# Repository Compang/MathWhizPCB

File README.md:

# MathWhizPCB
PCB designed for ONU research

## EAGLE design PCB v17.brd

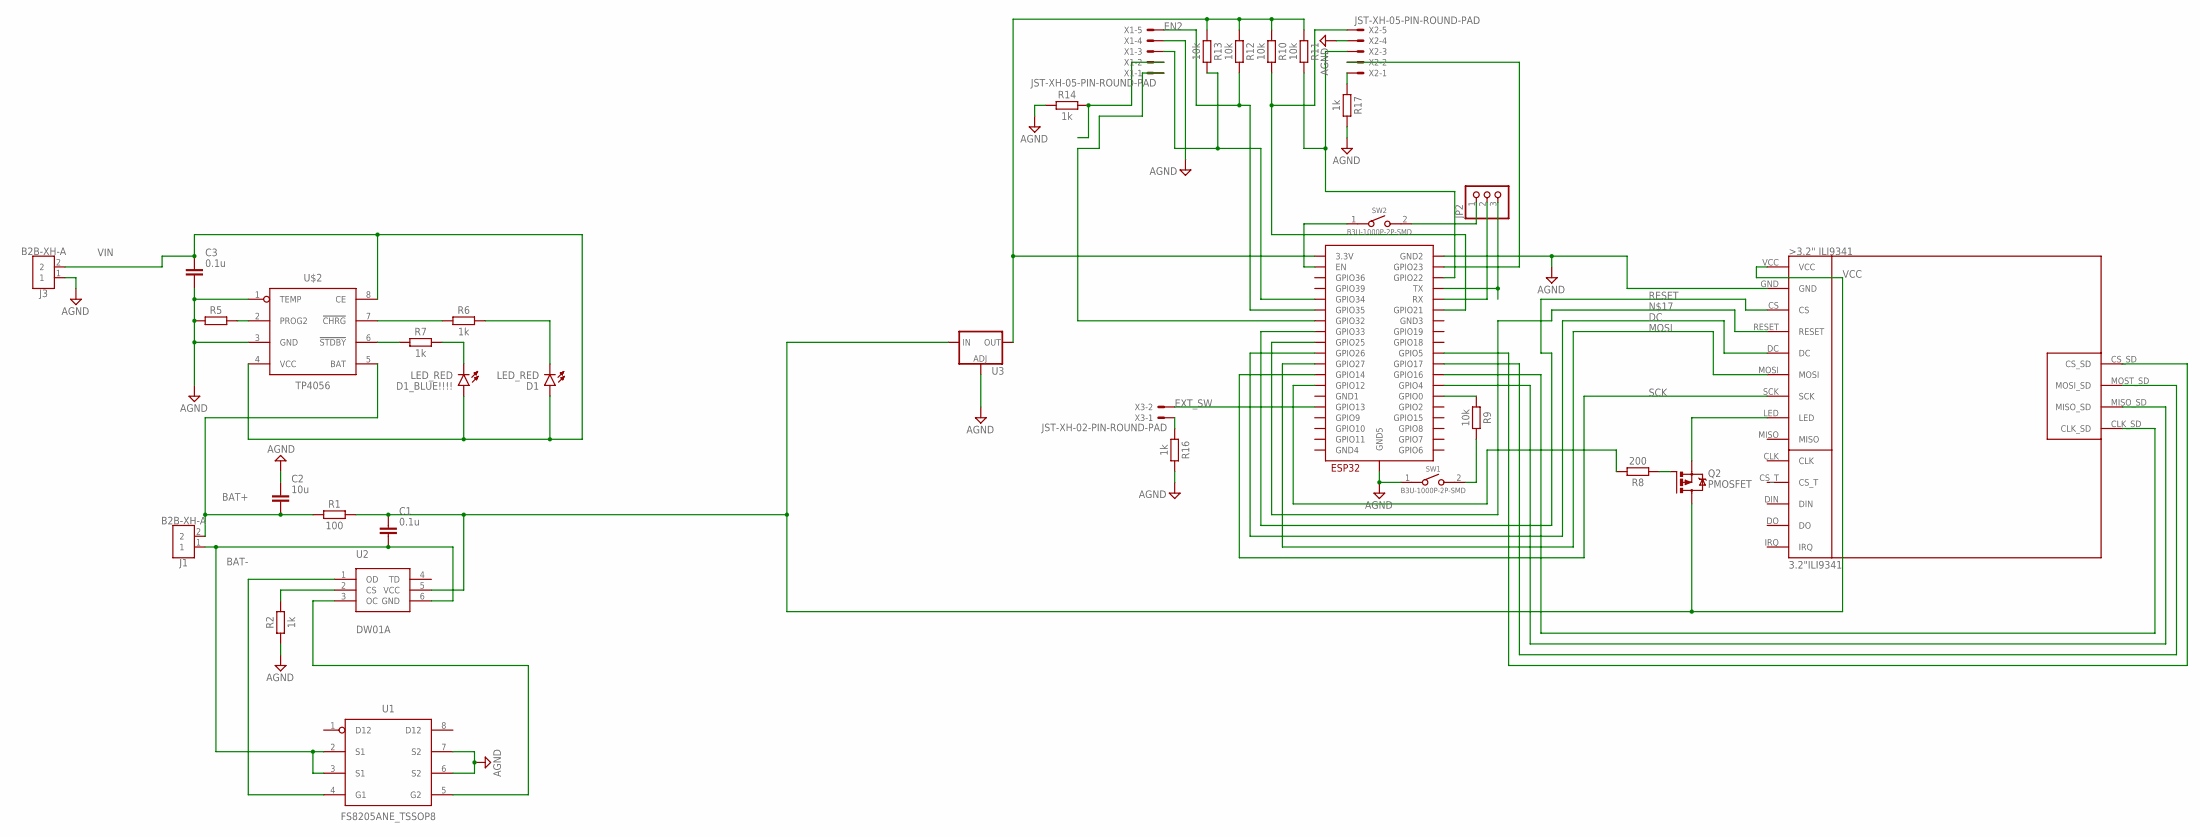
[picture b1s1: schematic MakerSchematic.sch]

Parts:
C1, C3: 0.1u; CAPC1608X85
C2: 10u; CAPC1608X85
D1, D1_BLUE!!!!: LED_RED; LEDC2012X110N_FLAT-R
J1, J3: B2B-XH-A
JP2: PINHD-1X3/90; 1X03/90
Q2: PMOSFET; SOT23
R1: 100; RESC2012X65
R2, R6, R7, R14, R16, R17: 1k; RESC1608X60
R5: R_CHIP-0603(1608-METRIC); RESC1608X60
R8: 200; RESC2012X65
R9, R10, R11, R12, R13: 10k; RESC1608X60
SW1, SW2: B3U-1000P-2P-SMD; SW2-2.6-3.0X2.5X1.2+0.4MM
U1: FS8205ANE_TSSOP8; SOP65P640X120-8
U2: DW01A
U3: V_REG_LM1117SOT223; SOT223
U$1: ESP32-WROOM
U$2: TP4056; SOIC127P601X152-8N
U$3: 3.2"ILI9341
X1, X2: JST-XH-05-PIN-ROUND-PAD; JST-XH-05-PACKAGE-ROUND-PAD
X3: JST-XH-02-PIN-ROUND-PAD; JST-XH-02-PACKAGE-ROUND-PAD

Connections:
AGND: C2.1, C3.2, J3.1, R2.1, R5.1, R14.1, R16.2, R17.2, SW1.1, U1.6 (S2), U1.7 (S2), U3.1 (ADJ), U$1.GND2, U$1.GND5, U$2.1 (TEMP), U$2.3 (GND), U$3.GND, X1.4, X2.4
BAT+: C2.2, J1.2, R1.1, U$2.5 (BAT)
BAT-: C1.2, J1.1, U1.2 (S1), U1.3 (S1), U2.6 (GND)
D12: U1.8 (D12)
DC: U$1.IO26 (GPIO26), U$3.DC
EN2: R12.2, U$1.IO35 (GPIO35), X1.5
EXT_SW: U$1.IO13 (GPIO13), X3.2
MOSI: U$1.IO27 (GPIO27), U$3.MOSI
unnamed: R10.1, R11.1, R12.1, R13.1, U3.2 (OUT), U3.4 (OUT), U$1.3V3 (3.3V)
unnamed: U1.4 (G1), U2.1 (OD)
unnamed: U1.5 (G2), U2.3 (OC)
unnamed: R2.2, U2.2 (CS)
unnamed: R6.1, U$2.7 (!CHRG)
unnamed: R5.2, U$2.2 (PROG2)
unnamed: D1_BLUE!!!!.C, R7.2
unnamed: R7.1, U$2.6 (!STDBY)
unnamed: D1.C, R6.2
unnamed: R9.1, U$1.IO0 (GPIO0)
unnamed: JP2.2, U$1.RX
unnamed: JP2.3, U$1.TX
unnamed: SW2.1, U$1.EN
unnamed: R8.2, U$1.IO12 (GPIO12)
unnamed: U$1.IO25 (GPIO25), U$3.RESET
unnamed: R17.1, X2.1
unnamed: Q2.1 (G), R8.1
unnamed: JP2.1, SW2.2
unnamed: R10.2, U$1.IO21 (GPIO21), X2.5
unnamed: R13.2, U$1.IO34 (GPIO34), X1.3
unnamed: U$1.IO23 (GPIO23), X2.2
unnamed: U$1.IO32 (GPIO32), X1.1
unnamed: R9.2, SW1.2
unnamed: Q2.2 (S), U$3.LED
unnamed: U$1.IO17 (GPIO17), U$3.MOST_SD (MOSI_SD)
unnamed: U$1.IO16 (GPIO16), U$3.CLK_SD
unnamed: R14.2, X1.2
unnamed: R16.1, X3.1
unnamed: U$1.IO4 (GPIO4), U$3.MISO_SD
unnamed: U$1.IO5 (GPIO5), U$3.CS_SD
RESET: U$1.IO33 (GPIO33), U$3.CS
SCK: U$1.IO14 (GPIO14), U$3.SCK
VCC: C1.1, Q2.3 (D), R1.2, U2.5 (VCC), U3.3 (IN), U$3.VCC
VIN: C3.1, D1.A, D1_BLUE!!!!.A, J3.2, U$2.4 (VCC), U$2.8 (CE)
YOURMOM: R11.2, U$1.IO22 (GPIO22), X2.3

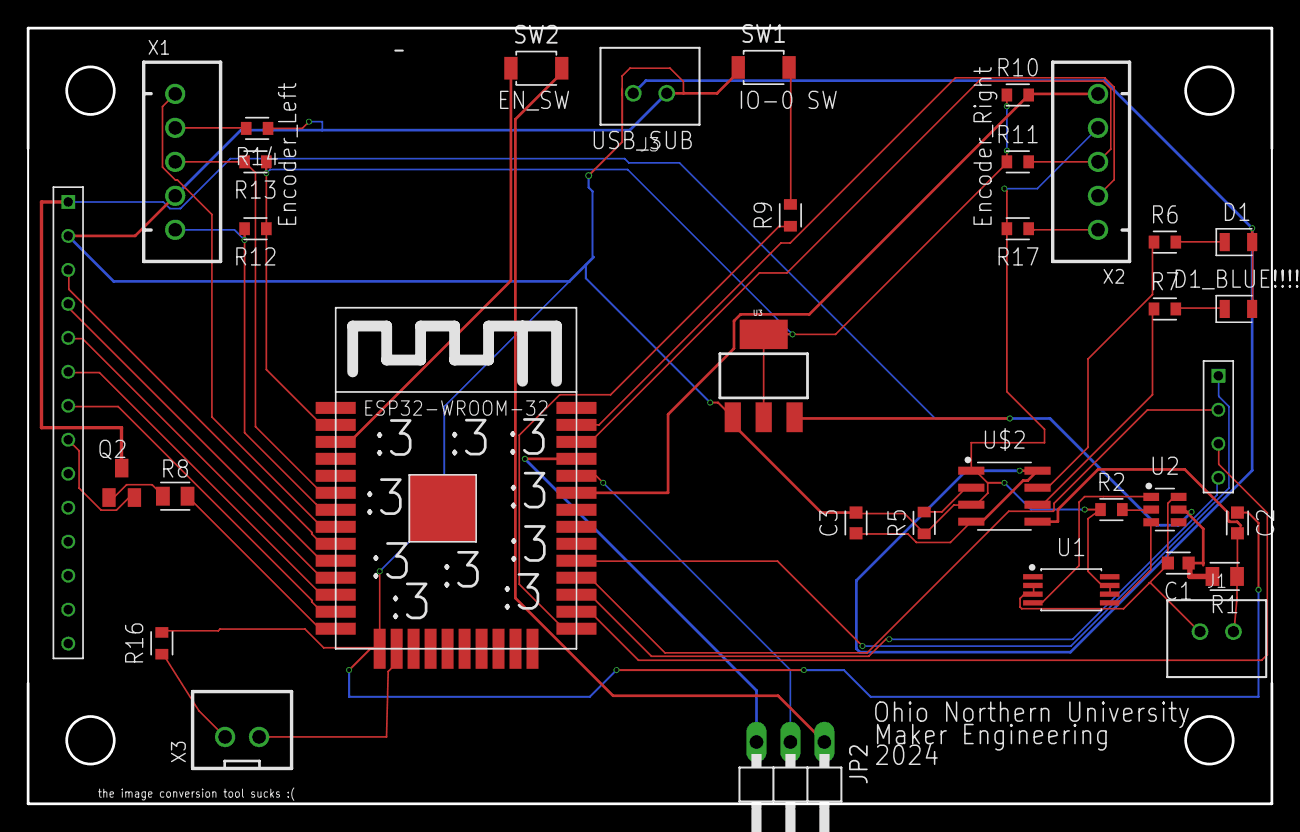
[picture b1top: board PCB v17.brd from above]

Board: 2 copper layers, 93.0 x 58.0 mm, 34 parts (0 on the bottom side), 42 nets.

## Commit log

2025-03-20 Uploaded final design files
    Project was managed during prototyping in Fusion

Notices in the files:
parts and their libraries:
SparkFun-IC-Power: Licensing: Creative Commons ShareAlike 4.0 International - https://creativecommons.org/licenses/by-sa/4.0
